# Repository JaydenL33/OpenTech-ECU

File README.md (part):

# OpenTech-ECU

**A Rust-first, open-source engine management platform: a deterministic virtual ECU, auditable fuel calibration, evidence-gated ignition, and a human-approved tuning copilot.**

> **Status: v0.1, virtual-first.** The host Rust core, headless CLI, local service, browser/Electron tuning studio, local read-only copilot, and a `no_std` STM32 safety skeleton are present. There is no target firmware image, no physical output path, and no vehicle actuation. Nothing in this repository is an engine-safe calibration.

OpenTech-ECU is a new, original aftermarket ECU platform. It is being built as a Rust port/reimplementation of Speeduino behavior, with a feature target informed by modern VCU-class capabilities and Link G5 Voodoo Pro-class workflows, and a tuning workflow designed around explainable and reviewable changes rather than hidden auto-tuning.

**Not a Speeduino fork.** OpenTech-ECU is a separate, Rust-first project based on Speeduino. The original Speeduino C++ tree is retained in `speeduino/`, `test/`, `reference/`, `lib/`, and `boards/` as a behavioral oracle for parity testing. It is not the product firmware, and it has not been replaced or deleted. Upstream Speeduino is at <https://github.com/speeduino/speeduino>; its documentation describes the reference tree, not this Rust platform.

## Why this is different

1. **Virtual ECU first, deterministic by construction.** A 1 ms host simulation runs a physics-lite four-stroke engine, a configurable missing-tooth crank decoder with cam phase, a 720-degree injection/ignition scheduler, a wideband model with transport delay, sensor lag, noise and fault injection, and an independent protection state machine. The loop uses fixed 1 ms steps and seeded noise so runs are reproducible; determinism is a design requirement, not a hard real-time guarantee.

2. **Fuel calibration you can audit.** Closed-loop short-term trim, cell/bank-aware long-term trim, and an offline Mixture Map share one learning-gate implementation. Proposals are bounded, show sample counts and confidence, distinguish measured from unvisited cells, account for active trims, and expose a diff for preview. Apply requires explicit human approval in the service, creates a new sealed calibration revision, and records it (plus every apply, undo, resample, table edit and rejected attempt) in a local append-only, hash-chained, checksum-verified revision/audit store that survives restart. That store is local evidence, not a signed certification.

3. **Ignition refuses to guess.** Lambda is never an ignition input. A synthetic ignition table exists only to make the simulator run; physical ignition export is blocked. A recommendation requires a licensed, engine-specific verified reference, and still requires timing-light verification and knock review. The ignition API has no lambda parameter by design.

4. **An LLM copilot with a hard trust boundary.** The Mastra/TypeScript copilot can read telemetry and logs, run Mixture Map analysis, and explain gates and DTCs. It cannot write a calibration, change ignition, disable a protection, or touch hardware. Its output is schema-validated untrusted input; a human approves every apply. It also runs in a deterministic offline tool mode with no API key.

5. **A real tuning UI, not a mock.** The repository includes a React/TypeScript/Vite tuning studio with live telemetry, editable maps and 3D surfaces, Mixture Map review, diagnostics, logs, and a Copilot client page. An Electron desktop shell launches the local Rust service and presents the UI; it is not Tauri, and it was not launch-tested in this headless environment.

6. **Evidence over claims.** The project distinguishes implemented, simulated, planned, and hardware-blocked work. See the [feature matrix](docs/FEATURE-MATRIX.md), [porting strategy](docs/PORTING-FROM-SPEEDUINO.md), [safety case](docs/SAFETY-CASE.md), and the source specification in [ECU_MASTER_BRIEF.md](ECU_MASTER_BRIEF.md).

## Status at a glance

Status terms: **Implemented** means host-side code exists and type-checks; it is not a claim of completed verification, parity, or hardware readiness. **Simulated** means the behavior exists only inside the virtual ECU. **Planned** means design only. **Blocked** means prohibited or impossible until hardware and independent validation exist.

| Area | Status | Notes |
|---|---|---|
| Rust workspace | Implemented, host-only | `cargo fmt`, `cargo clippy`, and `cargo test --workspace` pass (244 tests); see the verification note. |
| Deterministic virtual ECU | Simulated | 1 ms physics-lite engine, trigger generation, scheduler, wideband lag/delay/faults, protection, telemetry; six built-in scenarios. |
| Calibration and tables | Implemented, host-only | 1D–4D tables, clamped interpolation, axis resampling, validation, SHA-256 sealed revisions, table diffs, starter wizard, preflight, durable local revision/audit history. |
| Lambda fuel calibration | Implemented, host-only | Shared gates, bounded STFT, cell/bank-aware LTFT, offline Mixture Map with hard-fault abstention, confidence, proposal preview, selective apply and undo. |
| Ignition policy | Implemented, host-only | Evidence-gated recommendations; synthetic simulation-only tables; physical export blocked. |
| Engine protection | Implemented, host-only | 14 DTCs, latching, freeze frames, warning/derate/limp/cut reactions. |
| Protocol | Implemented, served locally | JSON/WebSocket envelopes and a length-delimited binary frame with CRC32; the local service exposes the JSON link. |
| `ecu-sim-cli` | Implemented, verified | Scenario runner, deterministic replay check, Mixture Map analysis and approval-gated apply. See the quick start. |
| `studio-service` | Implemented, local-only | Axum HTTP/WebSocket service for live telemetry, calibration edits/undo, axis resampling, log replay, preflight, Mixture Map, faults, logs and a bench harness view. Calibration revisions and audit entries persist to a local append-only store; live simulation/session state is in memory. No auth/TLS. |
| Tuning Studio (browser + Electron) | Implemented, verified UI | React/TypeScript/Vite app; `npm run build` and headless browser smoke tests pass. Includes the black/yellow support-style shell, maps, Mixture Map, diagnostics, logs and a Harness & I/O page. `electron/main.cjs` is a desktop shell; it was not launch-tested (no display). Tauri is not used. |
| Harness & I/O | Implemented, unreviewed source | `config/harness/opentech-bench-harness.json` is generated from the unreviewed KiCad BOM/pin/test-point exports; `ecu-harness` validates the generated manifest. No OEM pinout, no vendor map data, no vehicle adapter. |
| Mastra tuning copilot | Implemented, local-only | `apps/tuning-copilot`: read-only tools, structured output, `ignitionAdvice: none`, and a deterministic offline mode. LLM mode is opt-in with an API key. Per-request tool audit only; no durable audit store. |
| Firmware / embedded target | Implemented, skeleton | `ecu/firmware/stm32`: `no_std` safety skeleton with capture-to-decoder path, protection, and fail-closed `EngineOutputs`. The `thumbv7em-none-eabihf` check passes. No HAL, timer capture, drivers, watchdog, flash, or target image. |
| Durable audit / persistence | Implemented (host, local) | Append-only revision + audit store with hash chain and SHA-256 verification on load; tamper/corruption refused at startup (`AUDIT/TUNING_WORKSTREAM_EVIDENCE.md` round 8). Not signed, no authentication, tail truncation undetectable without an external anchor. |
| Physical injector/coil actuation | Blocked | `PHYSICAL_OUTPUT_INTERLOCK_ENGAGED = true`; no code path energizes hardware. |
| Bench hardware design | H2 complete with exceptions; H3 not ready | `hardware/prototype-v1/`: routed Speeduino v0.4.4d SMD review copy, 0 unconnected, ERC 49, DRC 397 + 199 per-item exclusions, 3 M3 mounting holes, assembly/fab drawings, manufacturing exports. Focused independent review: ACCEPT WITH FINDINGS. 11 BOM MPNs, footprint audit and human mechanical/fabrication acceptance remain. Legacy `hardware/kicad/evo8-bench-ecu` remains an unrouted draft (499 unconnected, 14 DRC) and is not the baseline. Not fabrication-approved. |
| Vehicle use | Blocked | No bench, engine, EMC, or functional-safety validation. |

### Verification note

Verified on 2026-11-13 with the native Rust toolchain and the local GCC wrapper (`/home/jlee/tools/bin/cc`; no system compiler is installed):

- `cargo fmt --all -- --check` — pass.
- `cargo clippy --workspace --all-targets --locked -- -D warnings` — pass.
- `cargo test --workspace --locked` — 244 passed, 0 failed. This includes the bounded crank/cam loss vectors (RUST-TRG-001) and the durable calibration-store tests (TUNE-AUD-01).
- `cargo test -p ecu-trigger --locked -- --nocapture` — 29 passed; 0 post-acquisition non-sequential edges at 150/250/400 rpm.
- `cargo test -p studio-service --locked -- --nocapture` — 36 passed, including restart, tamper-refusal, SIGKILL crash-proxy and failed-write rollback tests.
- `cargo check -p opentech-firmware-stm32 --target thumbv7em-none-eabihf --no-default-features` — pass. This is a compile check for the `no_std` skeleton, not hardware validation.
- CLI `mixture_sweep` — determinism PASS, 2184 frames byte-identical; `analyze` produced 3–4 bounded cells; `apply --approve` produced sealed revision 2.
- Tuning Studio — `npm run build` passes. A headless Chromium smoke test opened the black/yellow shell, Fuel map, Harness page, Mixture Map, Setup, Diagnostics, Logs and Copilot with no page errors. Screenshots are in `evidence/ui/`.
- Harness — `GET /api/harness` reports a valid bench manifest (29 connectors, 54 test points). The page is a documentation view only; no vendor map data is shipped.
- Copilot — `npx tsc --noEmit` passes; `npm test` now runs `tsc --noEmit` and passes. The offline `/api/copilot` path was exercised against the Rust service and returned tool-audit entries. LLM mode was not called.

The Electron shell was not launch-tested because this environment has no display. Axis resampling and replay endpoints/UI exist; the replay start/stop endpoints were exercised (658 frames queued), but full WebSocket playback was not independently inspected. Axis resampling was not exercised in this verification pass. Re-run the commands on a clean host before relying on these results.

## Reference vehicle and release gates

The target reference is a JDM Mitsubishi Lancer Evolution VIII GSR (CT9A, 4G63T, six-speed manual), but the specific ECU variant, connector count, pinout, trigger pattern, injector data, ignition topology, and harness are **UNVERIFIED**. `ecu-calibration/src/vehicle.rs` contains a simulator-only template for this profile; the physical configuration request is hard-blocked. It is not a plug-and-play definition and must not be used to build a harness or connect hardware.

**Current status: Gate 0 only. No vehicle connection, no harness construction, no ECU flashing, and no engine start are permitted.** Gate 0 is a software-readiness stage, not a safety certification.

Release gates follow [`ECU_MASTER_BRIEF.md`](ECU_MASTER_BRIEF.md) exactly:

| Gate | Scope | Current status |
|---|---|---|
| **0** | Software simulation | Current stage; host simulation, CLI, UI, copilot, and `no_std` skeleton checks |
| **1** | Unpowered hardware | No physical board. A routed prototype-v1 review copy exists (0 unconnected; ERC 49; DRC 397 + 199 documented exclusions; assembly/fab drawings), but BOM MPNs, footprint audit and human mechanical/fabrication acceptance are incomplete. Not fabrication-approved |
| **2** | Powered bench | Not started; no drivers, loads, or fault injection |
| **3** | Vehicle electrical compatibility | Blocked; ECU variant and pinout unverified |
| **4** | Controlled engine testing | Blocked; requires Gates 1–3 and independent review |
| **5** | Vehicle operation | Blocked; requires Gates 1–4, insurance/legal review, and validation |

Gate definitions are maintained in [release gates](AUDIT/RELEASE_GATES.md). Where an audit table uses older labels, the master-brief numbering above is authoritative. See also [vehicle compatibility](AUDIT/VEHICLE_COMPATIBILITY.md), [pinout verification](AUDIT/ECU_PINOUT_VERIFICATION.md), and [open issues](AUDIT/OPEN_ISSUES.md).

## Architecture

```
                        HOST / VIRTUAL-FIRST (today)

  +----------------------------+      +-------------------------------+
  | Tuning Studio (browser/Electron) |  | Tuning Copilot (offline/LLM)  |
  | React + TypeScript + Vite  |      | Mastra / TypeScript           |
  +-------------+--------------+      +---------------+---------------+
                |                                     |
                |  review, approve, undo              |  read-only tools,
                |                                     |  proposals, explanations
                v                                     v
  +-------------------------------------------------------------------+
  | studio-service (local Axum HTTP + WebSocket)                      |
  | telemetry, revisions, preflight, Mixture Map, faults, logs, UI    |
  +-------------------------------+-----------------------------------+
                                  |  ecu-protocol
                                  |  JSON envelopes + binary CRC32
                                  v
  +-------------------------------------------------------------------+
  | ecu-simulator: 1 ms deterministic loop                            |
  | trigger -> scheduler -> fuel/ignition -> protection -> telemetry  |
  +------+-----------+-----------+-----------+-----------+------------+
         |           |           |           |           |
   ecu-trigger  ecu-fuel  ecu-ignition  ecu-lambda  ecu-protection
         +-----------+-----------+-----------+-----------+
                         ecu-types / ecu-calibration
                         ecu-protocol / ecu-diagnostics

  ---------------------------------------------------------------------
  firmware/stm32 (no_std skeleton; no HAL/drivers) -> physical I/O blocked
```

The virtual ECU is the integration point: it owns the engine plant, sensors, trigger wheel, wideband, and simulated actuators, while the control crates compute fuel, spark, learning decisions, and protection reactions. The host protocol is a new, versioned protocol; it is not Speeduino's TunerStudio serial protocol and does not write raw ECU memory.

Detailed layering, data flow, host/firmware boundaries, and the copilot trust boundary are in [docs/ARCHITECTURE.md](docs/ARCHITECTURE.md).

## Safety non-negotiables

1. **No physical actuation in v0.1.** A `no_std` STM32 safety skeleton exists, but it has no HAL, timer capture/compare, injector or ignition drivers, flashing path, or vehicle interface. `PHYSICAL_OUTPUTS_AUTHORISED` is false and outputs are forced off; preflight reports the physical export blocked.
2. **Lambda is never ignition evidence.** A wideband sensor measures combustion oxygen/fueling consequences. It cannot establish MBT, knock margin, or safe spark advance. No automatic spark advance is permitted, and physical ignition export is blocked.
3. **Fuel corrections are bounded and reviewable.** Learning gates cover engine state, sensor validity, fuel/oil pressure, injector duty, misfire, exhaust leak, overrun, knock, overboost, and DTC state; the offline Mixture Map additionally enforces steady-state rate checks by default. Proposals are previewed, selectively applied, and sealed into a new revision; the service keeps an undo history and persists every revision and audit entry to a local, tamper-evident (not signed) store.
4. **The LLM is not in the control loop.** Copilot output is untrusted, schema-validated input. The copilot cannot apply changes, change ignition, disable gates or protections, clear latched faults, or access hardware.
5. **Calibrations are estimates until proven otherwise.** Starter VE, target-lambda, and dwell values are explicit engineering estimates. The synthetic ignition surface is simulation-only. A licensed reference and timing-light verification are required before any physical ignition use.
6. **No road, track, or engine use.** This is a development platform, not a certified or validated ECU. Independent engineering review, bench testing, and functional-safety work are mandatory before any physical deployment.

## Quick start

Requirements for a normal build host: Rust 1.80 or newer and a C linker (for example `build-essential` on Debian/Ubuntu). The repository workspace is under `ecu/`.

```bash
# From the repository root: headless virtual ECU.
cd ecu
cargo run -p ecu-sim-cli -- --help
cargo run -p ecu-sim-cli -- scenarios
cargo run -p ecu-sim-cli -- run --scenario mixture_sweep --out runs/sweep --check-determinism

# Analyze the log with the offline Mixture Map; emits a proposal, never applies.
cargo run -p ecu-sim-cli -- analyze \
  --log runs/sweep/log.json --cal runs/sweep/calibration.json \
  --out runs/sweep/report.json --min-samples 12

# Apply a reviewed proposal to a new sealed revision (virtual calibration only).
cargo run -p ecu-sim-cli -- apply \
  --cal runs/sweep/calibration.json --report runs/sweep/report.json \
  --out runs/sweep/calibration-applied.json --approve

# Local tuning service. Defaults to 127.0.0.1:8765 and serves the built UI.
cargo run -p studio-service -- --port 8765
```

The browser tuning studio lives in `ecu/apps/tuning-studio`:

```bash
cd ecu/apps/tuning-studio
npm install
npm run dev        # Vite on 127.0.0.1:5173, /api proxied to 127.0.0.1:8765
npm run build      # production build in dist/, served by studio-service
```

Tauri is not used because the WebKitGTK development libraries required for a Tauri build are unavailable in this environment. An Electron desktop shell (`ecu/apps/tuning-studio/electron/main.cjs`) starts the local service and loads the UI; it needs a desktop session and a built service, so it was not launch-tested here. The Copilot page talks to the Mastra service on port 8787. Start it in a third terminal:

```bash
cd ecu/apps/tuning-copilot
npm install

# Deterministic offline mode: no LLM, no API key. Requires the Rust service on 8765.
COPILOT_OFFLINE=1 npm run start

# Optional LLM mode: opt in explicitly and provide a provider key.
COPILOT_ENABLE_LLM=1 DEEPSEEK_API_KEY=... npm run start
```

The copilot has only read-only tools. It cannot apply a calibration; the Mixture Map page is the approval path.

To reproduce the verified host baseline: `cd ecu && cargo fmt --all -- --check && cargo clippy --workspace --all-targets -- -D warnings && cargo test --workspace`.

## What is implemented in the host core

| Crate | Responsibility |
|---|---|
| `ecu-types` | Unit-tagged quantities, engine/injector configuration, sensor quality and wideband state, telemetry frames, provenance, CSV log rows. |
| `ecu-calibration` | Rank 1–4 tables, clamped interpolation, axis validation, immutable calibration revisions, SHA-256 sealing, table diffs, starter wizard, preflight, ignition policy. |
| `ecu-fuel` | Speed-density air mass, target-lambda fuel mass, injector pulse width, dead time, pressure compensation, duty and minimum-pulse diagnostics, alpha-N/blended load. |
| `ecu-ignition` | Advance/dwell bounds, dwell-duty limiting, rev limiter with hysteresis, evidence-gated recommendations, simulation-only surfaces. |
| `ecu-trigger` | Configurable missing-tooth crank decoder, gap and dropped-tooth checks, cam-phase latching, sequential sync state machine, timeout to lost sync. |
| `ecu-scheduler` | Deterministic 720-degree injection, dwell, and spark events for 1–12 cylinders and arbitrary firing orders. |
| `ecu-lambda` | Shared learning gates, bounded STFT, cell/bank-aware LTFT, offline Mixture Map with exhaust-delay alignment, confidence, proposals, selective apply, and undo metadata. |
| `ecu-protection` | Independent 14-DTC protection state machine with latching, freeze frames, and bounded fuel/spark/boost/retard reactions. |
| `ecu-protocol` | Protocol version negotiation, JSON server events, binary framing with magic/version/flags/sequence/length/CRC32. |
| `ecu-simulator` | Physics-lite engine plant, trigger generation, sensor and wideband models, fault windows, closed-loop/LTFT integration, protection, deterministic telemetry logs. |
| `ecu-diagnostics` | Session ring buffer, event log, session summaries, deterministic replay cursor. |

### Applications

| Path | Responsibility |
|---|---|
| `apps/ecu-sim-cli` | Headless scenario runner, deterministic replay check, offline Mixture Map analysis, approval-gated apply, calibration verification. |
| `apps/studio-service` | Local Axum HTTP/WebSocket service: live telemetry, calibration revisions and undo, axis resampling (`/api/calibration/resample`), log replay (`/api/replay/start` and `/api/replay/stop`), preflight, Mixture Map analysis/apply, faults, CSV/log export, static UI hosting. |
| `apps/tuning-studio` | React/TypeScript/Vite UI: dashboard, fuel/target/ignition maps with axis resampling, 3D surface view, Mixture Map review/apply, setup, diagnostics, logs with replay control, calibration audit, Copilot client. `electron/main.cjs` is the desktop shell; it has no ECU logic or hardware access. |
| `apps/tuning-copilot` | Mastra/TypeScript copilot: read-only telemetry/fault/calibration/log/Mixture Map tools, structured answer schema, offline tool mode, optional LLM mode, per-request tool audit. |

## Repository layout

```text
OpenTech-ECU/
  README.md                 this document
  ECU_MASTER_BRIEF.md       source specification (not modified by the docs pass)
  docs/                     architecture, porting, feature matrix, copilot, safety, formulas, roadmap
  ecu/                      Rust Cargo workspace
    crates/                 eleven host library crates
    apps/ecu-sim-cli/       headless simulator and calibration CLI
    apps/studio-service/    local HTTP/WebSocket tuning service
    apps/tuning-studio/     React/TypeScript/Vite UI with Electron shell
    apps/tuning-copilot/    Mastra/TypeScript read-only copilot service
    firmware/stm32/         no_std safety skeleton (no HAL/drivers)
  AUDIT/                    independent audit drafts and open issues
  research/                 EVO VIII source research
  NOTICE.md                 provenance and licensing notice
  speeduino/                retained Speeduino C++ reference tree (GPL-2.0)
  test/                     retained Speeduino native/unit tests
  reference/                retained Speeduino INI, bootloaders, and reference data
  lib/                      retained Speeduino test dependencies (ArduinoFake)
  boards/                   retained Speeduino board definitions
```

## Documentation

- [Architecture](docs/ARCHITECTURE.md) — layers, data flow, protocol, simulation, host/firmware split, trust boundary.
- [Porting from Speeduino](docs/PORTING-FROM-SPEEDUINO.md) — what “based on Speeduino” means, oracle strategy, GPL obligations, comparison plan.
- [Feature matrix](docs/FEATURE-MATRIX.md) — Speeduino parity and modern ECU feature families, with honest status.
- [LLM tuning copilot](docs/LLM-COPILOT.md) — Mastra design, tools, schemas, approval flow, prompt-injection defenses, audit.
- [Safety case](docs/SAFETY-CASE.md) — v0.1 virtual-only argument, hazards, evidence status, unresolved validation, interlock release criteria.
- [Calibration workflow](docs/CALIBRATION.md) — profile creation, sealed revisions, table editing/resampling, Mixture Map apply.
- [Formulas](docs/FORMULAS.md) — implemented fuel, trim, mixture-map, ignition, dwell, and scheduler equations, with assumptions.
- [Speeduino parity](docs/PARITY.md) — retained C++ oracle, current formula-level evidence, and the planned compiled comparison harness.
- [Engineering log](docs/ENGINEERING-LOG.md) — factual milestone record, decisions, known gaps and next work.
- [Roadmap](docs/ROADMAP.md) — phased plan from the current host core to parity, embedded work, and validation.
- [ECU_MASTER_BRIEF.md](ECU_MASTER_BRIEF.md) — the source research and engineering mandate; preserved as the specification.

### Audit and research (outside `docs/`)

Audit documents are snapshot drafts. Where an audit file reports an older test result or gate status, the verification note above and a fresh command run take precedence.

- [Engine control safety argument](AUDIT/ENGINE_CONTROL_SAFETY.md) — independent audit draft; not a certification.
- [Failure mode analysis](AUDIT/FAILURE_MODE_ANALYSIS.md) — FMEA-style hazard review.
- [Electrical design review](AUDIT/ELECTRICAL_DESIGN_REVIEW.md) — power, grounding, and I/O review.
- [Hardware status](AUDIT/HARDWARE_STATUS.md) — what hardware does and does not exist, connect strategy, blockers.
- [Evo VIII bench test plan](AUDIT/EVO8_BENCH_TEST_PLAN.md) — unexecuted Gate 1/2 procedure.
- [ECU pinout verification](AUDIT/ECU_PINOUT_VERIFICATION.md) — connector and pin evidence status.
- [Release gates](AUDIT/RELEASE_GATES.md) — Gate 0–5 definitions and current status.
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
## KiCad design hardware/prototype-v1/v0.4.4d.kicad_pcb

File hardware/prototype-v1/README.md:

# Prototype v1 — Speeduino v0.4.4d SMD review copy

This is the **native KiCad 9 review copy** of the selected Speeduino v0.4.4d SMD
design. The electrical design is upstream. OpenTech-ECU saved it to KiCad 9
format, re-filled the copper zones and applied documented minimal revisions:
R-01…R-03 (PCB fixes) and R-04…R-10 (HW-H2-01: mounting holes, library links,
ERC annotation, DRC exclusions, fab drawing). The netlist is unchanged. It is
**not fabrication-approved**.

| Field | Value |
|---|---|
| Base design | Speeduino v0.4.4d SMD |
| Upstream commit | `ee6a9242834891877744ff2137663b6ca8d79ed6` |
| Preserved source | `../upstream-speeduino/v0.4.4d/` |
| KiCad | 9.0.9 |
| Board | 100.05 × 100.05 mm, 2-layer, 1.6 mm, 4 injector / 4 ignition, Arduino Mega 2560 shield, IDC40 |
| Mounting | H1–H3: 3.2 mm NPTH (M3) at three corners, 3.5 mm inset, 3.8 mm copper keep-out; no top-right hole (see `FABRICATION_NOTES.md` §3) |
| Routing | Complete: 0 unconnected items |
| ERC | 49 (4 errors, 45 warnings), all dispositioned — `verification/erc.rpt`, `AUDIT/PCB_CHECK_RESULTS.md` §3 |
| DRC | 397 reported (31 errors = JP6–JP11 jumpers, 366 warnings) + 199 per-item courtyard exclusions; 0 unconnected — `verification/drc.rpt`, `drc-with-exclusions.rpt` |
| Connectivity | PASS, 514/514 common nodes |
| Status | **H2 complete with documented exceptions, pending independent acceptance (not a pass); H3 not ready; not fabrication-approved** |

## Open the project

Open `v0.4.4d.kicad_pro` in KiCad 9.0.x. The root schematic
`v0.4.4d.kicad_sch` references the six hierarchical sheets in this directory.
The PCB is `v0.4.4d.kicad_pcb`.

`sym-lib-table` enables the bundled `v0.4.4c-rescue.lib`, which holds every
custom symbol. `fp-lib-table` enables three project-local footprint libraries
under `lib/`: `Shields`, `Misc` and `Speeduino_Legacy`. They were extracted
from the footprints embedded in the routed board (R-05), so library and board
copies match. The upstream `Connector_Automotive`/`IC_Automotive` libraries
were never in the upstream tree, nothing referenced them, and their table
entries have been removed.

## Reproduce the checks and exports

From the repository root:

```bash
hardware/tools/check_prototype_v1.sh
```

This runs, inside the pinned `kicad/kicad@sha256:e638b79b…7729` container:

- ERC on `v0.4.4d.kicad_sch`;
- DRC on `v0.4.4d.kicad_pcb`;
- DRC again with `--severity-exclusions` (excluded items + their comments);
- Gerber, drill (+ map + report), position, IPC-D-356, BOM, netlist and
  schematic PDF export;
- top/bottom assembly drawings, fab drawing, top/bottom 3D renders;
- schematic-to-PCB connectivity comparison;
- mounting-hole clearance check (`../tools/check_mounting_holes.py`).

The HW-H2-01 design edits are reproducible with
`../tools/apply_hw_h2_01_revision.py` (steps `sch`, `pcb`, `exclusions`). The
commands are in `../../AUDIT/HARDWARE_DIFF.md` §1.

Outputs are written to `verification/` and `manufacturing/`.

## Manufacturing package

| Directory | Contents |
|---|---|
| `manufacturing/gerbers/` | 9 Gerber layers + `.gbrjob` |
| `manufacturing/drill/` | Excellon drill file, drill map PDF, drill report, **fabrication drawing PDF** |
| `manufacturing/assembly/` | BOM CSV, position CSV (141 real placements, no proto pads/holes), IPC-D-356 net test, KiCad netlist, schematic PDF, **top/bottom assembly drawings** |
| `FABRICATION_NOTES.md` | Stack-up (upstream 2-layer 1.6 mm), stated assumptions, hole coordinates, drill summary, reflow vs hand-solder intent |

These are **review artefacts**. No board house has DFM-checked them, and
nothing has been manufactured. The BOM has 11 rows without MPNs; see
`HW-BOM-01`.

## What changed from upstream

1. Legacy `.sch` → native `.kicad_sch` (KiCad 9 save).
2. Legacy `.kicad_pcb` → native `.kicad_pcb` (KiCad 9 save).
3. Copper zones re-filled by the KiCad 9 zone filler (required for the format;
   removed 155 legacy clearance violations; netlist unchanged).
4. Bundled rescue symbol library enabled via `sym-lib-table` and `fp-lib-table`
   copied for reference.
5. The 150 unannotated proto-area pads are marked exclude-from-BOM and
   exclude-from-position-files. This is assembly metadata only; no copper
   change.
6. R-01: four starved-thermal GND pads (C5.2, C10.2, C11.2, U4.3) set to a
   solid zone connection.
7. R-02: duplicate 0.552 mm VDDA track segment removed.
8. R-03: two U5 MAP-sensor mechanical tabs converted from PTH to NPTH.
9. R-04: H1–H3 M3 NPTH mounting holes + 3.8 mm copper keep-outs.
10. R-05: project-local footprint libraries; C19 relinked to
    `Speeduino_Legacy:` (same pads).
11. R-06: `Device:CP1` → `Device:C_Polarized_US` (identical symbol).
12. R-07: 5 PWR_FLAGs at real power entry points.
13. R-08: 29 no-connects on unused pins; dangling ICSP labels, 2 wire stubs
    and 1 stray no-connect removed.
14. R-09: 199 per-item courtyard DRC exclusions with comments.
15. R-10: fab-drawing dimensions/notes on User.Drawings.

No component value, net, routing topology or outline edit was made. The
schematic netlist partition is identical to before. R-01…R-03 are reproducible
with `../tools/apply_v1_minimal_revision.py`, and R-04…R-10 with
`../tools/apply_hw_h2_01_revision.py`. All are recorded in
`../../AUDIT/HARDWARE_DIFF.md` §2. Full provenance:
`../../AUDIT/UPSTREAM_PROVENANCE.md`. Full check disposition:
`../../AUDIT/PCB_CHECK_RESULTS.md`.

## Do not

- Do not fabricate this board without independent review and explicit human H4
  approval.
- Do not connect it to an Evo VIII; the vehicle interface is unverified.
- Do not treat ERC/DRC as automotive safety evidence.

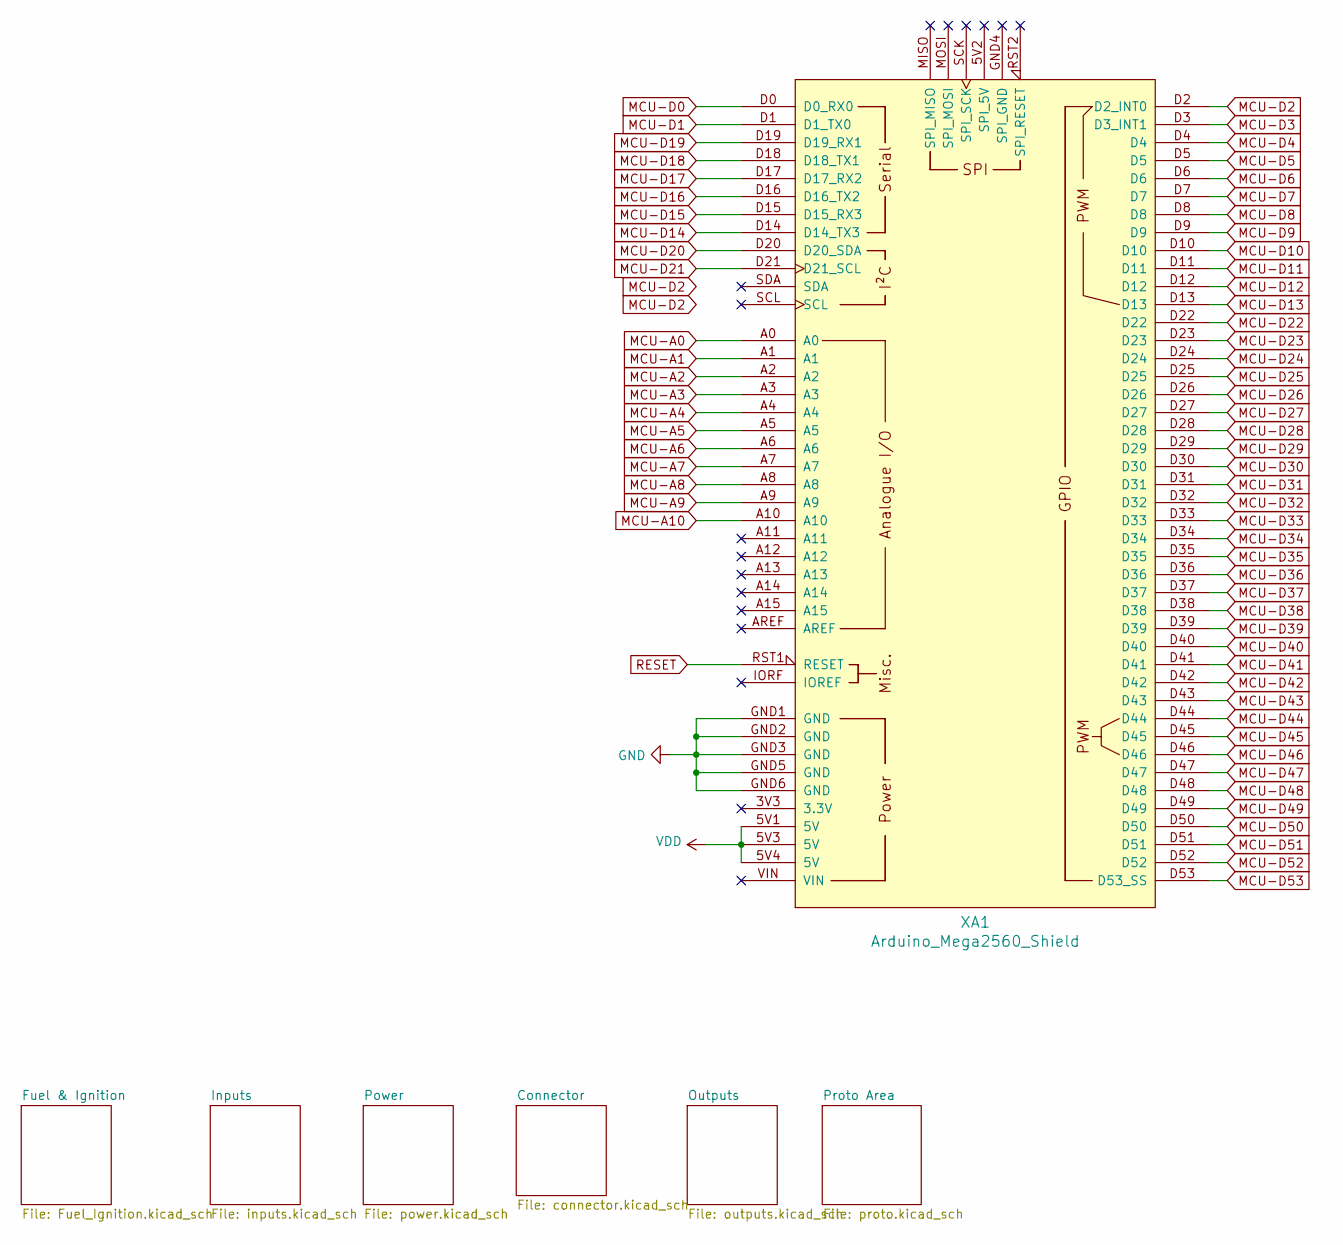
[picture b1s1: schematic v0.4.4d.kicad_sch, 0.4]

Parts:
XA1: Arduino_Mega2560_Shield; Arduino_Mega2560_Shield_IO_Only

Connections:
ADC-Clamp-1: XA1.A4; also elsewhere on the board
ADC-Clamp-2: XA1.A3; also elsewhere on the board
ADC-Clamp-3: XA1.A1; also elsewhere on the board
ADC-Clamp-4: XA1.A2; also elsewhere on the board
ADC-Clamp-5: XA1.A0; also elsewhere on the board
ADC-Clamp-6: XA1.A8; also elsewhere on the board
ADC-Clamp-8: XA1.D18 (D18_TX1); also elsewhere on the board
ADC-Clamp-9: XA1.D19 (D19_RX1); also elsewhere on the board
ADC-Clamp-10: XA1.D2 (D2_INT0); also elsewhere on the board
ADC-Clamp-13: XA1.D51; also elsewhere on the board
GND: XA1.GND1 (GND), XA1.GND2 (GND), XA1.GND3 (GND), XA1.GND5 (GND), XA1.GND6 (GND); also elsewhere on the board
MCU-A5: XA1.A5; also elsewhere on the board
MCU-A6: XA1.A6
MCU-A7: XA1.A7
MCU-A9: XA1.A9; also elsewhere on the board
MCU-A10: XA1.A10; also elsewhere on the board
MCU-D0: XA1.D0 (D0_RX0); also elsewhere on the board
MCU-D1: XA1.D1 (D1_TX0); also elsewhere on the board
MCU-D3: XA1.D3 (D3_INT1); also elsewhere on the board
MCU-D4: XA1.D4; also elsewhere on the board
MCU-D5: XA1.D5; also elsewhere on the board
MCU-D6: XA1.D6; also elsewhere on the board
MCU-D7: XA1.D7; also elsewhere on the board
MCU-D8: XA1.D8; also elsewhere on the board
MCU-D9: XA1.D9; also elsewhere on the board
MCU-D10: XA1.D10; also elsewhere on the board
MCU-D11: XA1.D11; also elsewhere on the board
MCU-D12: XA1.D12
MCU-D13: XA1.D13
MCU-D14: XA1.D14 (D14_TX3)
MCU-D15: XA1.D15 (D15_RX3)
MCU-D16: XA1.D16 (D16_TX2); also elsewhere on the board
MCU-D17: XA1.D17 (D17_RX2); also elsewhere on the board
MCU-D20: XA1.D20 (D20_SDA); also elsewhere on the board
MCU-D21: XA1.D21 (D21_SCL); also elsewhere on the board
MCU-D22: XA1.D22
MCU-D23: XA1.D23
MCU-D24: XA1.D24; also elsewhere on the board
MCU-D25: XA1.D25
MCU-D26: XA1.D26
MCU-D27: XA1.D27
MCU-D28: XA1.D28
MCU-D29: XA1.D29
MCU-D30: XA1.D30
MCU-D31: XA1.D31
MCU-D32: XA1.D32
MCU-D33: XA1.D33
MCU-D34: XA1.D34
MCU-D35: XA1.D35
MCU-D36: XA1.D36
MCU-D37: XA1.D37
MCU-D38: XA1.D38; also elsewhere on the board
MCU-D39: XA1.D39
MCU-D40: XA1.D40; also elsewhere on the board
MCU-D41: XA1.D41
MCU-D42: XA1.D42
MCU-D43: XA1.D43
MCU-D44: XA1.D44
MCU-D45: XA1.D45; also elsewhere on the board
MCU-D46: XA1.D46
MCU-D47: XA1.D47; also elsewhere on the board
MCU-D48: XA1.D48
MCU-D49: XA1.D49; also elsewhere on the board
MCU-D50: XA1.D50; also elsewhere on the board
MCU-D52: XA1.D52; also elsewhere on the board
MCU-D53: XA1.D53 (D53_SS)
RESET: XA1.RST1 (RESET); also elsewhere on the board
VDD: XA1.5V1 (5V), XA1.5V3 (5V), XA1.5V4 (5V); also elsewhere on the board

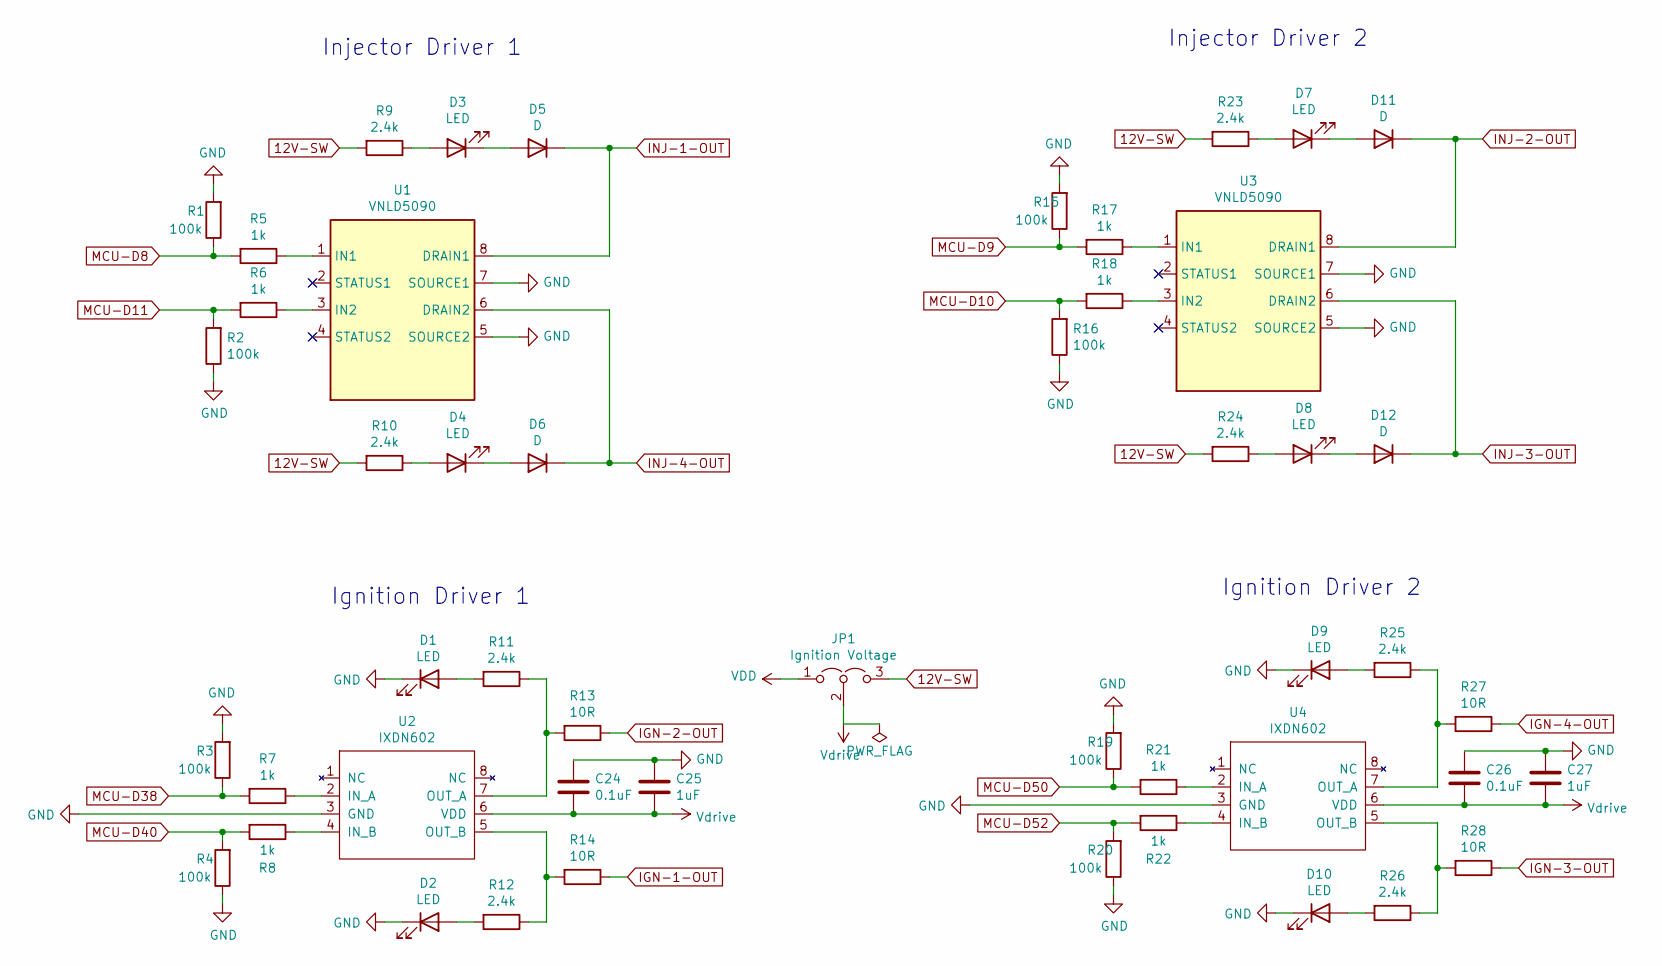
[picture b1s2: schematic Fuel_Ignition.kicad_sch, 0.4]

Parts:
C24, C26: 0.1uF; C_0805_2012Metric; Manufacturer_Part_Number CC0805KRX7R9BB104; Digikey Part Number 311-1140-1-ND
C25, C27: 1uF; C_0805_2012Metric; Manufacturer_Part_Number CC0805KKX7R7BB105; Digikey Part Number 311-1365-1-ND
D1, D2, D3, D4, D7, D8, D9, D10: LED; LED_0805_2012Metric; Manufacturer_Part_Number LH R974-LP-1; Digikey Part Number 475-1415-1-ND
D5, D6, D11, D12: D; D_SOD-323; Manufacturer_Part_Number 1N4448WX-TP; Digikey Part Number 1N4448WXTPMSCT-ND
JP1: Ignition Voltage; PinHeader_1x03_P2.54mm_Vertical; Manufacturer_Part_Number M20-9990345; Digikey Part Number 952-2263-ND
R1, R2, R3, R4, R15, R16, R19, R20: 100k; R_0805_2012Metric; Manufacturer_Part_Number RC0805FR-07100KL; Digikey Part Number 311-100KCRCT-ND
R5, R6, R7, R8, R17, R18, R21, R22: 1k; R_0805_2012Metric; Manufacturer_Part_Number RC0805FR-071KL; Digikey Part Number 311-1.00KCRCT-ND
R9, R10, R11, R12, R23, R24, R25, R26: 2.4k; R_0805_2012Metric; Manufacturer_Part_Number RC0805FR-072K4L; Digikey Part Number 311-2.40KCRCT-ND
R13, R14, R27, R28: 10R; R_1206_3216Metric; Manufacturer_Part_Number RC1206FR-0710RL; Digikey Part Number 311-10.0FRCT-ND
U1, U3: VNLD5090; SOIC-8_3.9x4.9mm_P1.27mm; Manufacturer_Part_Number VNLD5090-E; Digikey Part Number 497-18682-ND
U2, U4: IXDN602; SOIC-8_3.9x4.9mm_P1.27mm; Manufacturer_Part_Number IXDN602SIATR; Digikey Part Number 212-IXDN602SIACT-ND

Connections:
12V-SW: JP1.3 (B), R9.2, R10.2, R23.2, R24.2; also elsewhere on the board
GND: C24.1, C25.1, C26.1, C27.1, D1.1 (K), D2.1 (K), D9.1 (K), D10.1 (K), R1.2, R2.1, R3.2, R4.1, R15.2, R16.1, R19.2, R20.1, U1.5 (SOURCE2), U1.7 (SOURCE1), U2.3 (GND), U3.5 (SOURCE2), U3.7 (SOURCE1), U4.3 (GND); also elsewhere on the board
IGN-1-OUT: R14.1; also elsewhere on the board
IGN-2-OUT: R13.1; also elsewhere on the board
IGN-3-OUT: R28.1; also elsewhere on the board
IGN-4-OUT: R27.1; also elsewhere on the board
INJ-1-OUT: D5.1 (K), U1.8 (DRAIN1); also elsewhere on the board
INJ-2-OUT: D11.1 (K), U3.8 (DRAIN1); also elsewhere on the board
INJ-3-OUT: D12.1 (K), U3.6 (DRAIN2); also elsewhere on the board
INJ-4-OUT: D6.1 (K), U1.6 (DRAIN2); also elsewhere on the board
MCU-D8: R1.1, R5.2; also elsewhere on the board
MCU-D9: R15.1, R17.2; also elsewhere on the board
MCU-D10: R16.2, R18.2; also elsewhere on the board
MCU-D11: R2.2, R6.2; also elsewhere on the board
MCU-D38: R3.1, R7.2; also elsewhere on the board
MCU-D40: R4.2, R8.2; also elsewhere on the board
MCU-D50: R19.1, R21.2; also elsewhere on the board
MCU-D52: R20.2, R22.2; also elsewhere on the board
unnamed: D1.2 (A), R11.2
unnamed: D2.2 (A), R12.2
unnamed: D3.1 (K), D5.2 (A)
unnamed: D3.2 (A), R9.1
unnamed: D4.1 (K), D6.2 (A)
unnamed: D4.2 (A), R10.1
unnamed: D7.2 (A), R23.1
unnamed: D8.2 (A), R24.1
unnamed: D9.2 (A), R25.2
unnamed: D10.2 (A), R26.2
unnamed: D7.1 (K), D11.2 (A)
unnamed: D8.1 (K), D12.2 (A)
unnamed: R5.1, U1.1 (IN1)
unnamed: R6.1, U1.3 (IN2)
unnamed: R7.1, U2.2 (IN_A)
unnamed: R8.1, U2.4 (IN_B)
unnamed: R11.1, R13.2, U2.7 (OUT_A)
unnamed: R12.1, R14.2, U2.5 (OUT_B)
unnamed: R17.1, U3.1 (IN1)
unnamed: R18.1, U3.3 (IN2)
unnamed: R21.1, U4.2 (IN_A)
unnamed: R22.1, U4.4 (IN_B)
unnamed: R25.1, R27.2, U4.7 (OUT_A)
unnamed: R26.1, R28.2, U4.5 (OUT_B)
VDD: JP1.1 (A); also elsewhere on the board
Vdrive: C24.2, C25.2, C26.2, C27.2, JP1.2 (C), U2.6 (VDD), U4.6 (VDD)

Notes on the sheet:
Injector Driver 2
Ignition Driver 1
Ignition Driver 2
Injector Driver 1

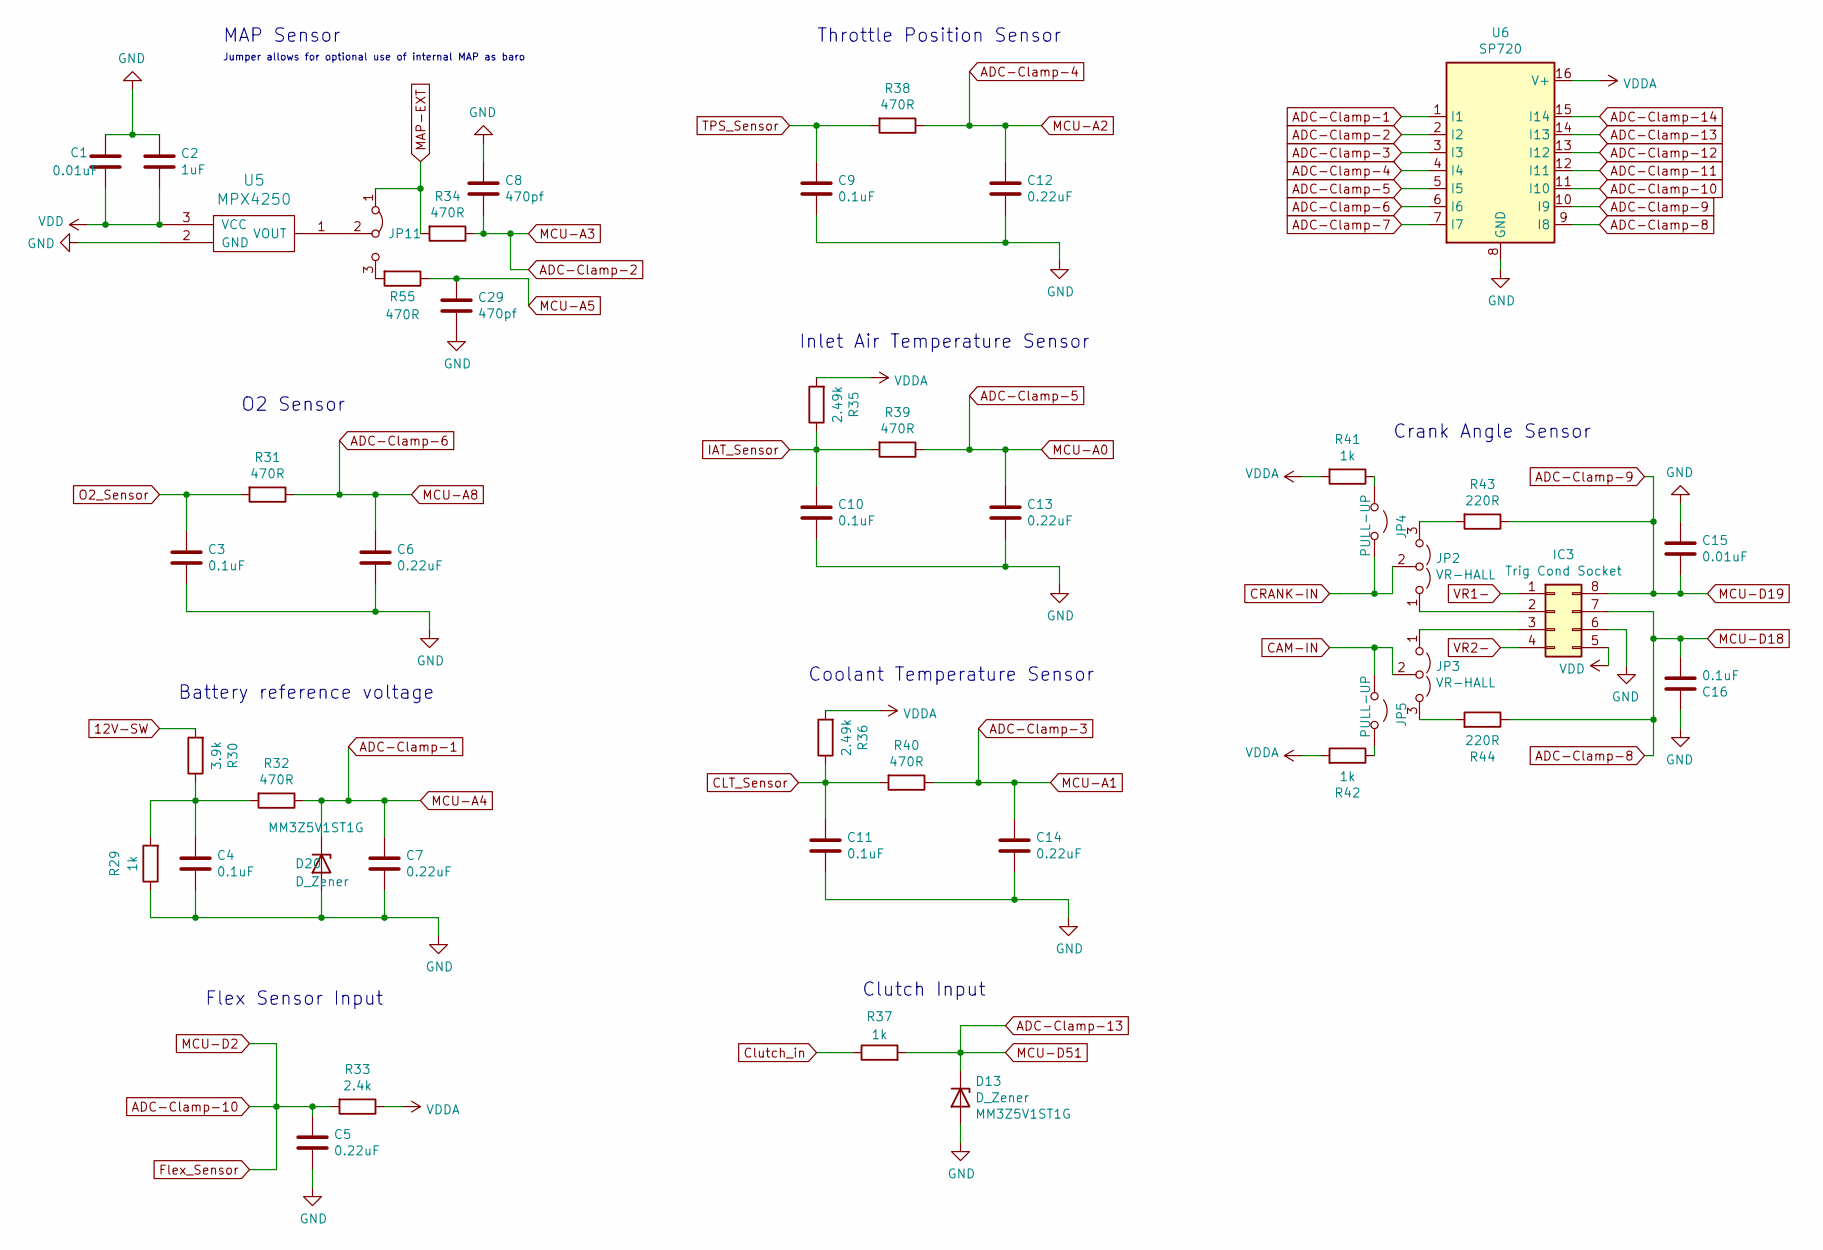
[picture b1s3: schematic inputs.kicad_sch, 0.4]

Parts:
C1, C15: 0.01uF; C_0805_2012Metric; Manufacturer_Part_Number CC0805KRX7R9BB103; Digikey Part Number 311-1136-1-ND
C2: 1uF; C_0805_2012Metric; Manufacturer_Part_Number CC0805KKX7R7BB105; Digikey Part Number 311-1365-1-ND
C3, C4, C9, C10, C11, C16: 0.1uF; C_0805_2012Metric; Manufacturer_Part_Number CC0805KRX7R9BB104; Digikey Part Number 311-1140-1-ND
C5, C6, C7, C12, C13, C14: 0.22uF; C_0805_2012Metric; Manufacturer_Part_Number CL21B224KOCNNNC; Digikey Part Number 1276-1284-1-ND
C8, C29: 470pf; C_0805_2012Metric; Manufacturer_Part_Number CC0805KRX7R9BB471; Digikey Part Number 311-1124-1-ND
D13, D20: D_Zener; D_SOD-323; Part # MM3Z5V1ST1G; Digikey Part Number MM3Z5V1ST1GOSCT-ND
IC3: Trig Cond Socket; DIP-8_W7.62mm_Socket
JP2, JP3: VR-HALL; PinHeader_1x03_P2.54mm_Vertical; Manufacturer_Part_Number M20-9990345; Digikey Part Number 952-2263-ND
JP4, JP5: PULL-UP; PinHeader_1x02_P2.54mm_Vertical; Manufacturer_Part_Number M20-9990245; Digikey Part Number 952-2261-ND
JP11: Jumper_3_Bridged12; SolderJumper-3_P1.3mm_Bridged12_RoundedPad1.0x1.5mm
R29, R37, R41, R42: 1k; R_0805_2012Metric; Manufacturer_Part_Number RC0805FR-071KL; Digikey Part Number 311-1.00KCRCT-ND
R30: 3.9k; R_0805_2012Metric; Manufacturer_Part_Number RC0805FR-073K9L; Digikey Part Number 311-3.90KCRCT-ND
R31, R32, R34, R38, R39, R40, R55: 470R; R_0805_2012Metric; Manufacturer_Part_Number ERJ-6ENF4700V; Digikey Part Number P470CCT-ND
R33: 2.4k; R_0805_2012Metric; Manufacturer_Part_Number RC0805FR-072K4L; Digikey Part Number 311-2.40KCRCT-ND
R35, R36: 2.49k; R_0805_2012Metric; Manufacturer_Part_Number RT0805BRD072K49L; Digikey Part Number YAG1854CT-ND
R43, R44: 220R; R_0805_2012Metric; Manufacturer_Part_Number RC0805FR-07220RL; Digikey Part Number 311-220CRCT-ND
U5: MPX4250; Manufacturer_Part_Number MPX4250AP; Digikey Part Number MPX4250AP-ND
U6: SP720; SOIC-16_3.9x9.9mm_P1.27mm; Manufacturer_Part_Number SP720ABTG; Digikey Part Number F3162CT-ND

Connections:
12V-SW: R30.2; also elsewhere on the board
ADC-Clamp-1: C7.1, D20.1 (K), R32.1, U6.1 (I1); also elsewhere on the board
ADC-Clamp-2: C8.2, R34.1, U6.2 (I2); also elsewhere on the board
ADC-Clamp-3: C14.1, R40.1, U6.3 (I3); also elsewhere on the board
ADC-Clamp-4: C12.1, R38.1, U6.4 (I4); also elsewhere on the board
ADC-Clamp-5: C13.1, R39.1, U6.5 (I5); also elsewhere on the board
ADC-Clamp-6: C6.1, R31.1, U6.6 (I6); also elsewhere on the board
ADC-Clamp-7: U6.7 (I7)
ADC-Clamp-8: C16.2, IC3.7, R44.1, U6.9 (I8); also elsewhere on the board
ADC-Clamp-9: C15.2, IC3.8, R43.1, U6.10 (I9); also elsewhere on the board
ADC-Clamp-10: C5.1, R33.2, U6.11 (I10); also elsewhere on the board
ADC-Clamp-11: U6.12 (I11)
ADC-Clamp-12: U6.13 (I12)
ADC-Clamp-13: D13.1 (K), R37.2, U6.14 (I13); also elsewhere on the board
ADC-Clamp-14: U6.15 (I14)
CAM-IN: JP3.2 (C), JP5.1 (A); also elsewhere on the board
CLT_Sensor: C11.1, R36.1, R40.2; also elsewhere on the board
CRANK-IN: JP2.2 (C), JP4.1 (A); also elsewhere on the board
Clutch_in: R37.1; also elsewhere on the board
GND: C1.1, C2.1, C3.2, C4.2, C5.2, C6.2, C7.2, C8.1, C9.2, C10.2, C11.2, C12.2, C13.2, C14.2, C15.1, C16.1, C29.2, D13.2 (A), D20.2 (A), IC3.6, R29.1, U5.2 (GND), U6.8 (GND); also elsewhere on the board
IAT_Sensor: C10.1, R35.1, R39.2; also elsewhere on the board
MAP-EXT: JP11.1 (A), R34.2; also elsewhere on the board
MCU-A5: C29.1, R55.1; also elsewhere on the board
unnamed: C4.1, R29.2, R30.1, R32.2
unnamed: IC3.2, JP2.1 (A)
unnamed: IC3.3, JP3.1 (A)
unnamed: JP2.3 (B), R43.2
unnamed: JP3.3 (B), R44.2
unnamed: JP4.2 (B), R41.1
unnamed: JP5.2 (B), R42.1
unnamed: JP11.2 (C), U5.1 (VOUT)
unnamed: JP11.3 (B), R55.2
O2_Sensor: C3.1, R31.2; also elsewhere on the board
TPS_Sensor: C9.1, R38.2; also elsewhere on the board
VDD: C1.2, C2.2, IC3.5, U5.3 (VCC); also elsewhere on the board
VDDA: R33.1, R35.2, R36.2, R41.2, R42.2, U6.16 (V+); also elsewhere on the board
VR1-: IC3.1; also elsewhere on the board
VR2-: IC3.4; also elsewhere on the board

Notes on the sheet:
Flex Sensor Input
Jumper allows for optional use of internal MAP as baro
Battery reference voltage
Coolant Temperature Sensor
Clutch Input
Crank Angle Sensor
Throttle Position Sensor
MAP Sensor
O2 Sensor
Inlet Air Temperature Sensor

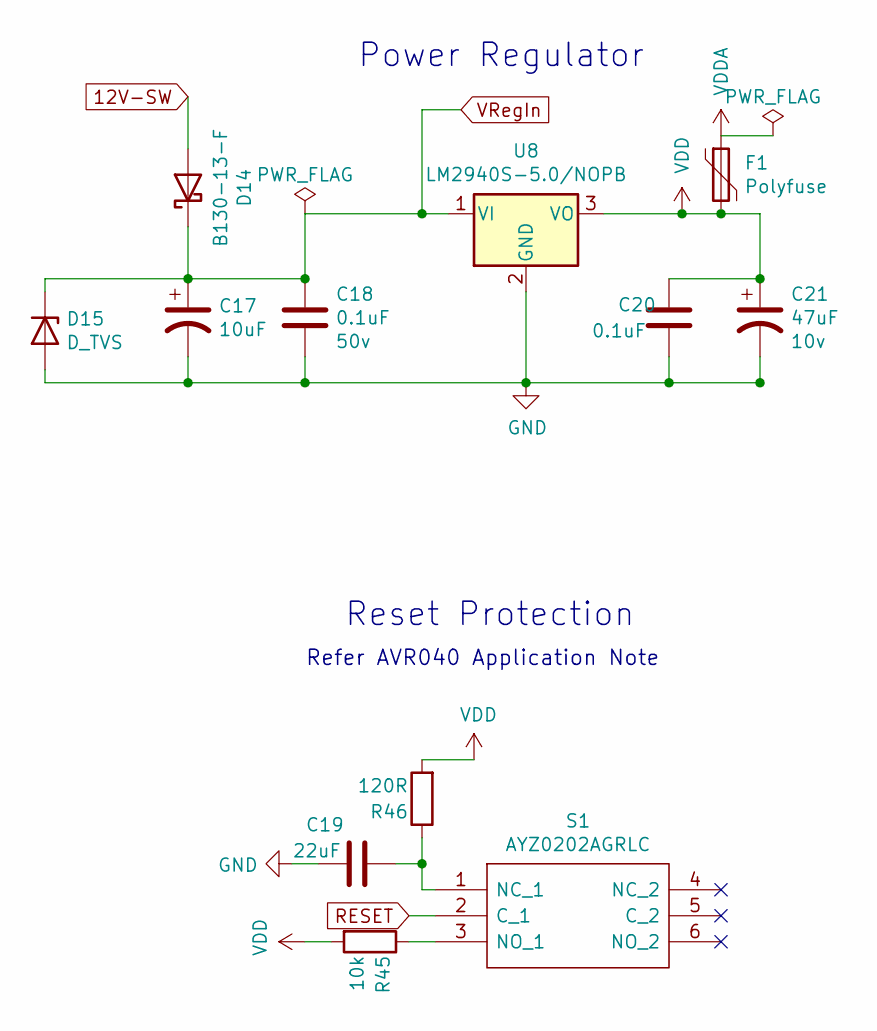
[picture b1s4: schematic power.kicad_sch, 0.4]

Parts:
C17: 10uF; CP_EIA-7343-31_Kemet-D; Voltage 35v; Manufacturer_Part_Number T491D106K050AT; Digikey Part Number 399-8361-1-ND
C18: 0.1uF; C_0805_2012Metric; Voltage 50v; Manufacturer_Part_Number CC0805KRX7R9BB104; Digikey Part Number 311-1140-1-ND
C19: 22uF; C_0805_2012Metric_Pad1.15x1.40mm_HandSolder; Manufacturer_Part_Number CL21A226KQCLRNC; Digikey Part Number 1276-6687-1-ND
C20: 0.1uF; C_0805_2012Metric; Manufacturer_Part_Number CC0805KRX7R9BB104; Digikey Part Number 311-1140-1-ND
C21: 47uF; CP_EIA-3528-21_Kemet-B; Voltage 10v; Manufacturer_Part_Number TAJB476K006RNJ; Digikey Part Number 478-1692-1-ND
D14: B130-13-F; D_SMA; Manufacturer_Part_Number B130-13-F; Digikey Part Number B130-FDICT-ND
D15: D_TVS; D_SMB; Manufacturer_Part_Number SMBJ40A-Q; Digikey Part Number SMBJ40A-QCT-ND
F1: Polyfuse; Fuse_1812_4532Metric; Manufacturer_Part_Number 0ZCC0050FF2C; Digikey Part Number 507-1361-1-ND
R45: 10k; R_0805_2012Metric; Manufacturer_Part_Number RC0805JR-0710KL; Digikey Part Number 311-10KARCT-ND
R46: 120R; R_0805_2012Metric; Manufacturer_Part_Number RC0805FR-07120RL; Digikey Part Number 311-120CRCT-ND
S1: AYZ0202AGRLC; Manufacturer_Part_Number AYZ0202AGRLC; Digikey Part Number 401-2013-1-ND
U8: LM2940S-5.0/NOPB; TO-263-3_TabPin2; Manufacturer_Part_Number LM2940S-5.0/NOPB; Digikey Part Number LM2940S-5.0/NOPB-ND

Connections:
12V-SW: D14.2 (A); also elsewhere on the board
GND: C17.2, C18.2, C19.2, C20.2, C21.2, D15.2 (A), U8.2 (GND); also elsewhere on the board
unnamed: C19.1, R46.1, S1.1 (NC_1)
unnamed: R45.1, S1.3 (NO_1)
RESET: S1.2 (C_1); also elsewhere on the board
VDD: C20.1, C21.1, F1.2, R45.2, R46.2, U8.3 (VO); also elsewhere on the board
VDDA: F1.1; also elsewhere on the board
VRegIn: C17.1, C18.1, D14.1 (K), D15.1 (K), U8.1 (VI)

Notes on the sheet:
Refer AVR040 Application Note
Power Regulator
Reset Protection

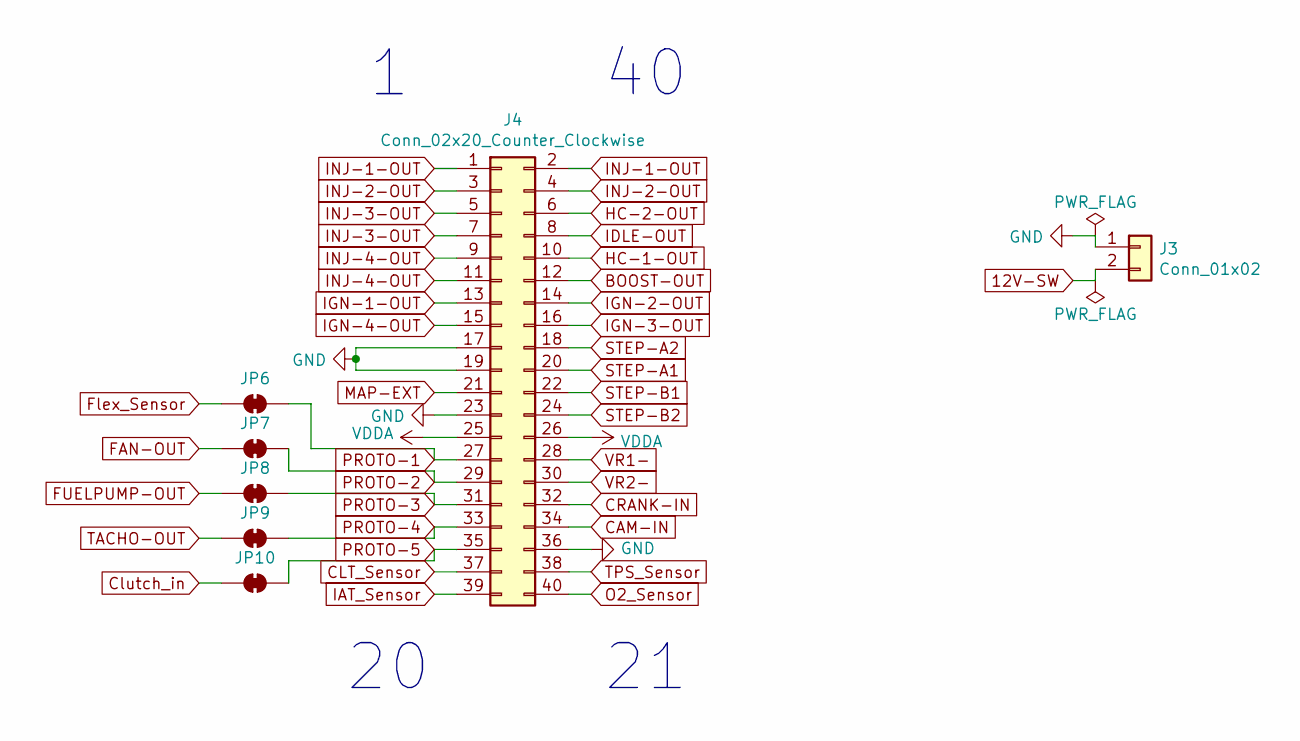
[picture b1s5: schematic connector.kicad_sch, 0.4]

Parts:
J3: Conn_01x02; TerminalBlock_Phoenix_PT-1,5-2-5.0-H_1x02_P5.00mm_Horizontal
J4: Conn_02x20_Counter_Clockwise; IDC-Header_2x20_P2.54mm_Vertical
JP6, JP7, JP8, JP9, JP10: SolderJumper_2_Bridged; SolderJumper-2_P1.3mm_Bridged_Pad1.0x1.5mm

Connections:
12V-SW: J3.2; also elsewhere on the board
ADC-Clamp-10: JP6.1 (A); also elsewhere on the board
BOOST-OUT: J4.12; also elsewhere on the board
CAM-IN: J4.34; also elsewhere on the board
CLT_Sensor: J4.37; also elsewhere on the board
CRANK-IN: J4.32; also elsewhere on the board
Clutch_in: JP10.1 (A); also elsewhere on the board
FAN-OUT: JP7.1 (A); also elsewhere on the board
FUELPUMP-OUT: JP8.1 (A); also elsewhere on the board
GND: J3.1, J4.17, J4.19, J4.23, J4.36; also elsewhere on the board
HC-1-OUT: J4.10; also elsewhere on the board
HC-2-OUT: J4.6; also elsewhere on the board
IAT_Sensor: J4.39; also elsewhere on the board
IDLE-OUT: J4.8; also elsewhere on the board
IGN-1-OUT: J4.13; also elsewhere on the board
IGN-2-OUT: J4.14; also elsewhere on the board
IGN-3-OUT: J4.16; also elsewhere on the board
IGN-4-OUT: J4.15; also elsewhere on the board
INJ-1-OUT: J4.1, J4.2; also elsewhere on the board
INJ-2-OUT: J4.3, J4.4; also elsewhere on the board
INJ-3-OUT: J4.5, J4.7; also elsewhere on the board
INJ-4-OUT: J4.9, J4.11; also elsewhere on the board
MAP-EXT: J4.21; also elsewhere on the board
O2_Sensor: J4.40; also elsewhere on the board
PROTO-1: J4.27, JP6.2 (B); also elsewhere on the board
PROTO-2: J4.29, JP7.2 (B); also elsewhere on the board
PROTO-3: J4.31, JP8.2 (B); also elsewhere on the board
PROTO-4: J4.33, JP9.2 (B); also elsewhere on the board
PROTO-5: J4.35, JP10.2 (B); also elsewhere on the board
STEP-A1: J4.20; also elsewhere on the board
STEP-A2: J4.18; also elsewhere on the board
STEP-B1: J4.22; also elsewhere on the board
STEP-B2: J4.24; also elsewhere on the board
TACHO-OUT: JP9.1 (A); also elsewhere on the board
TPS_Sensor: J4.38; also elsewhere on the board
VDDA: J4.25, J4.26; also elsewhere on the board
VR1-: J4.28; also elsewhere on the board
VR2-: J4.30; also elsewhere on the board

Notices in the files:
README.md:
Licensing and provenance:
- The root [`LICENSE`](LICENSE) is the GNU General Public License, version 2, and is preserved.
- Original Rust code in `ecu/` is declared **GPL-2.0-or-later** in the workspace `Cargo.toml`, package metadata and `NOTICE.md`, matching the Speeduino reference licence.
- The retained Speeduino C++ tree is **GPL-2.0-or-later** per its file headers and remains under its original terms. It is not relicensed by this project.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
- Speeduino-derived hardware is subject to CERN-OHL-S-2.0.
hardware/prototype-v1/v0.4.4d.kicad_pcb:
© Josh Stewart  &
